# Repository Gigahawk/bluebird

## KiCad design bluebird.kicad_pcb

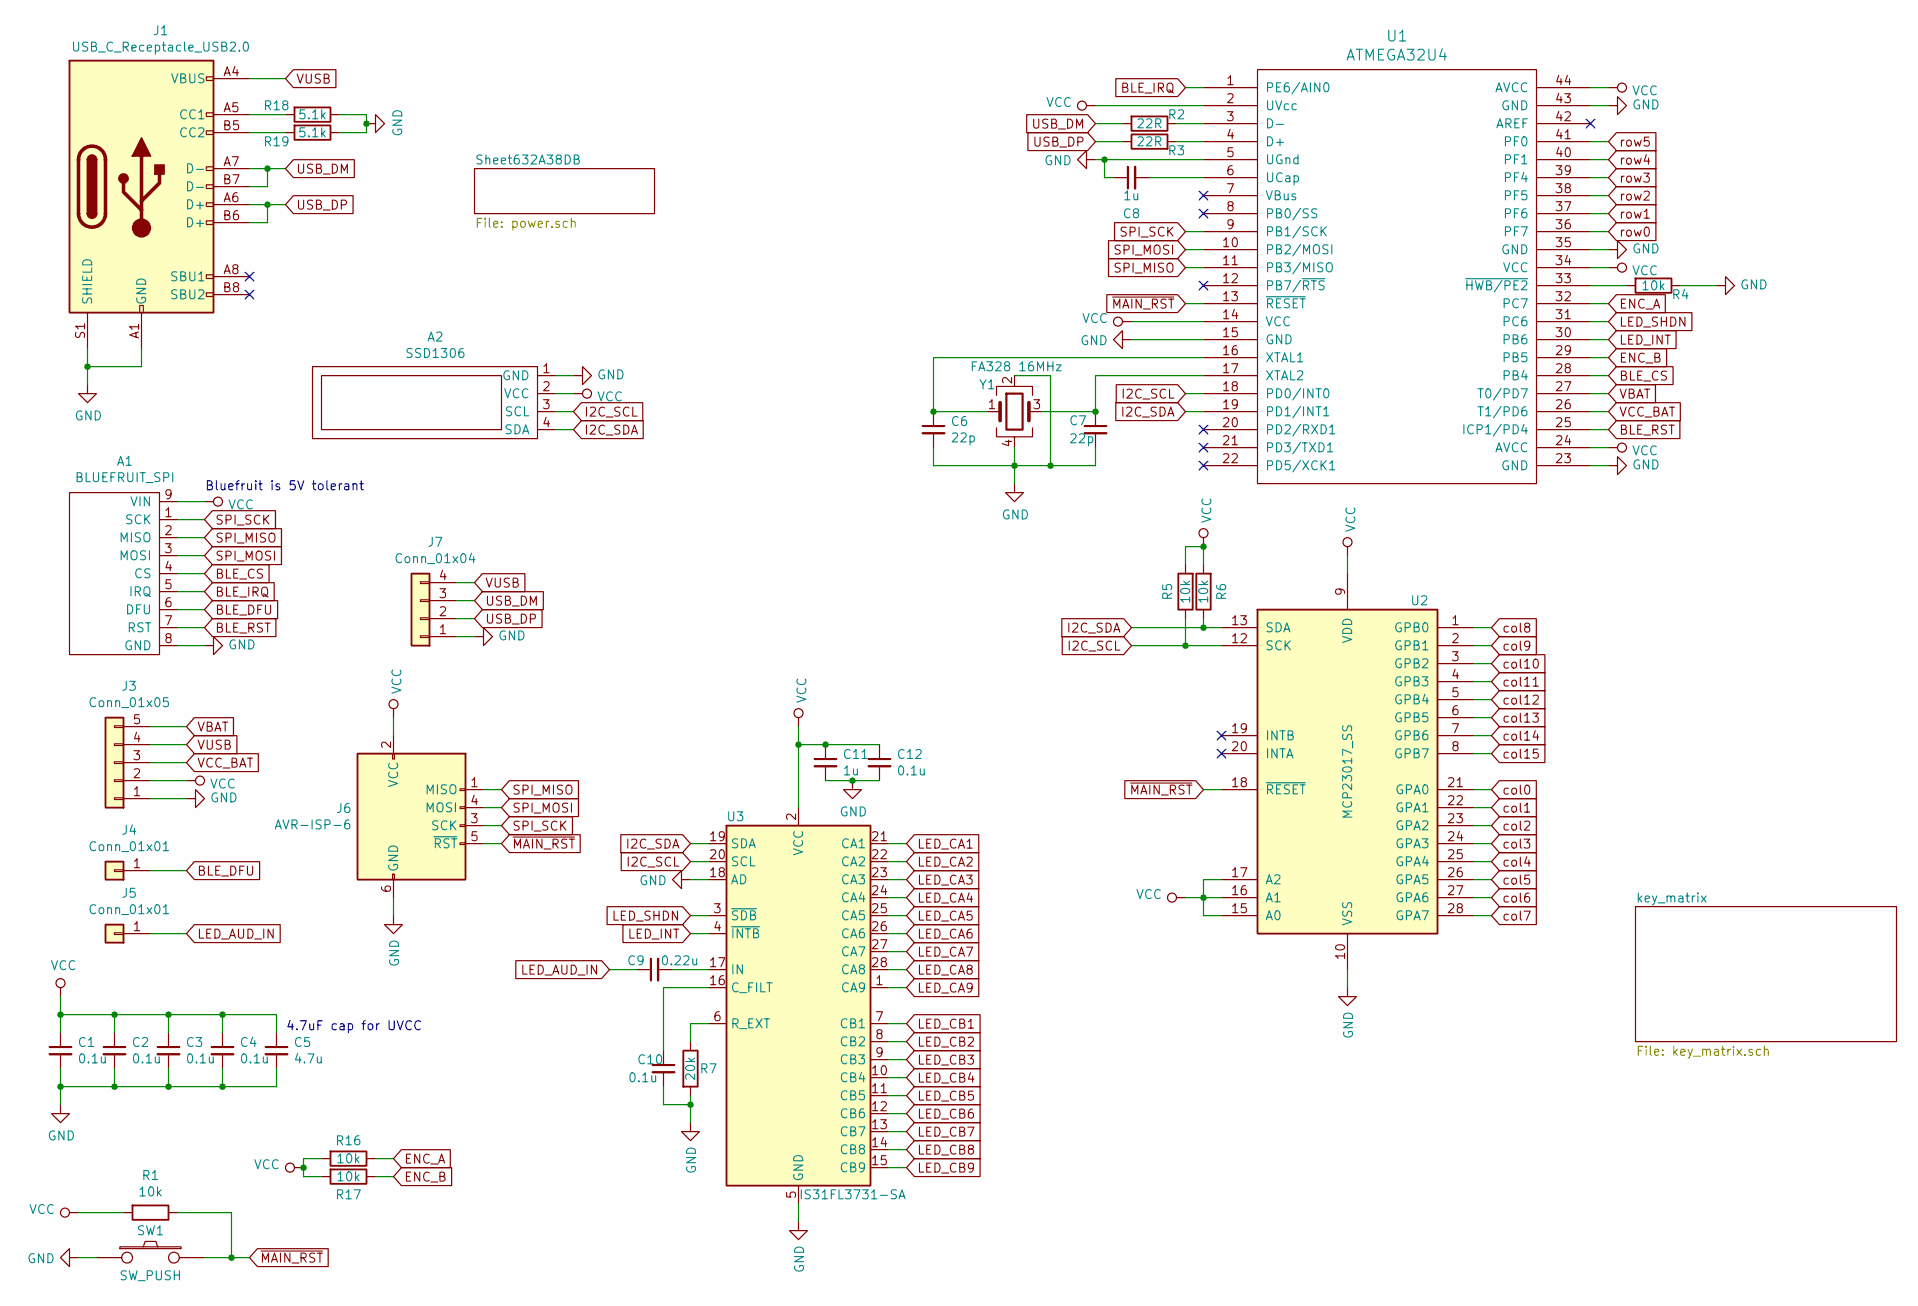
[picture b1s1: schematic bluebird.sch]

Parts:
A1: BLUEFRUIT_SPI; BLUEFRUIT_SPI_FRIEND
A2: SSD1306; SSD1306_128x32
C1, C2, C3, C4, C10, C12: 0.1u; C_0805_2012Metric_Pad1.15x1.40mm_HandSolder
C5: 4.7u; C_0805_2012Metric_Pad1.15x1.40mm_HandSolder
C6, C7: 22p; C_0805_2012Metric_Pad1.15x1.40mm_HandSolder
C8, C11: 1u; C_0805_2012Metric_Pad1.15x1.40mm_HandSolder
C9: 0.22u; C_0805_2012Metric_Pad1.15x1.40mm_HandSolder
J1: USB_C_Receptacle_USB2.0; USB_C_Receptacle_GCT_USB4085
J3: Conn_01x05; PinHeader_1x05_P2.54mm_Vertical
J4, J5: Conn_01x01; PinHeader_1x01_P2.54mm_Vertical
J6: AVR-ISP-6; AVR_ISP6
J7: Conn_01x04; PinHeader_1x04_P2.54mm_Vertical
R1, R4, R5, R6, R16, R17: 10k; R_0805_2012Metric_Pad1.15x1.40mm_HandSolder
R2, R3: 22R; R_0805_2012Metric_Pad1.15x1.40mm_HandSolder
R7: 20k; R_0805_2012Metric_Pad1.15x1.40mm_HandSolder
R18, R19: 5.1k; R_0805_2012Metric_Pad1.15x1.40mm_HandSolder
SW1: SW_PUSH; SW_SPST_TL3342
U1: ATMEGA32U4; TQFP-44_10x10mm_P0.8mm
U2: MCP23017_SS; SSOP-28_5.3x10.2mm_P0.65mm
U3: IS31FL3731-SA; SSOP-28_5.3x10.2mm_P0.65mm
Y1: FA328 16MHz; Crystal_SMD_SeikoEpson_FA238-4Pin_3.2x2.5mm_HandSoldering

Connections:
BLE_CS: A1.4 (CS), U1.28 (PB4)
BLE_DFU: A1.6 (DFU), J4.1
BLE_IRQ: A1.5 (IRQ), U1.1 (PE6/AIN0)
BLE_RST: A1.7 (RST), U1.25 (ICP1/PD4)
ENC_A: R16.1, U1.32 (PC7)
ENC_B: R17.1, U1.29 (PB5)
GND: A1.8 (GND), A2.1 (GND), C1.2, C2.2, C3.2, C4.2, C5.2, C6.2, C7.2, C8.1, C10.2, C11.2, C12.2, J1.A1 (GND), J1.A12 (GND), J1.B1 (GND), J1.B12 (GND), J1.S1 (SHIELD), J3.1, J6.6 (GND), J7.1, R4.1, R7.2, R18.1, R19.1, SW1.1, U1.5 (UGnd), U1.15 (GND), U1.23 (GND), U1.35 (GND), U1.43 (GND), U2.10 (VSS), U3.5 (GND), U3.18 (AD), Y1.2, Y1.4; also elsewhere on the board
I2C_SCL: A2.3 (SCL), R5.1, U1.18 (PD0/INT0), U2.12 (SCK), U3.20 (SCL)
I2C_SDA: A2.4 (SDA), R6.1, U1.19 (PD1/INT1), U2.13 (SDA), U3.19 (SDA)
LED_AUD_IN: C9.1, J5.1
LED_CA1: U3.21 (CA1); also elsewhere on the board
LED_CA2: U3.22 (CA2); also elsewhere on the board
LED_CA3: U3.23 (CA3); also elsewhere on the board
LED_CA4: U3.24 (CA4); also elsewhere on the board
LED_CA5: U3.25 (CA5); also elsewhere on the board
LED_CA6: U3.26 (CA6)
LED_CA7: U3.27 (CA7)
LED_CA8: U3.28 (CA8)
LED_CA9: U3.1 (CA9)
LED_CB1: U3.7 (CB1)
LED_CB2: U3.8 (CB2)
LED_CB3: U3.9 (CB3)
LED_CB4: U3.10 (CB4)
LED_CB5: U3.11 (CB5)
LED_CB6: U3.12 (CB6)
LED_CB7: U3.13 (CB7)
LED_CB8: U3.14 (CB8)
LED_CB9: U3.15 (CB9)
LED_INT: U1.30 (PB6), U3.4 (~INTB)
LED_SHDN: U1.31 (PC6), U3.3 (~SDB)
unnamed: C6.1, U1.16 (XTAL1), Y1.1
unnamed: C7.1, U1.17 (XTAL2), Y1.3
unnamed: C8.2, U1.6 (UCap)
unnamed: C9.2, U3.17 (IN)
unnamed: C10.1, U3.16 (C_FILT)
unnamed: J1.A5 (CC1), R18.2
unnamed: J1.B5 (CC2), R19.2
unnamed: R2.1, U1.3 (D-)
unnamed: R3.2, U1.4 (D+)
unnamed: R4.2, U1.33 (~HWB/PE2)
unnamed: R7.1, U3.6 (R_EXT)
SPI_MISO: A1.2 (MISO), J6.1 (MISO), U1.11 (PB3/MISO)
SPI_MOSI: A1.3 (MOSI), J6.4 (MOSI), U1.10 (PB2/MOSI)
SPI_SCK: A1.1 (SCK), J6.3 (SCK), U1.9 (PB1/SCK)
USB_DM: J1.A7 (D-), J1.B7 (D-), J7.3, R2.2
USB_DP: J1.A6 (D+), J1.B6 (D+), J7.2, R3.1
VBAT: J3.5, U1.27 (T0/PD7); also elsewhere on the board
VCC: A1.9 (VIN), A2.2 (VCC), C1.1, C2.1, C3.1, C4.1, C5.1, C11.1, C12.1, J3.2, J6.2 (VCC), R1.2, R5.2, R6.2, R16.2, R17.2, U1.2 (UVcc), U1.14 (VCC), U1.24 (AVCC), U1.34 (VCC), U1.44 (AVCC), U2.9 (VDD), U2.15 (A0), U2.16 (A1), U2.17 (A2), U3.2 (VCC); also elsewhere on the board
VCC_BAT: J3.3, U1.26 (T1/PD6); also elsewhere on the board
VUSB: J1.A4 (VBUS), J1.A9 (VBUS), J1.B4 (VBUS), J1.B9 (VBUS), J3.4, J7.4; also elsewhere on the board
col0: U2.21 (GPA0); also elsewhere on the board
col1: U2.22 (GPA1); also elsewhere on the board
col2: U2.23 (GPA2); also elsewhere on the board
col3: U2.24 (GPA3); also elsewhere on the board
col4: U2.25 (GPA4)
col5: U2.26 (GPA5)
col6: U2.27 (GPA6)
col7: U2.28 (GPA7)
col8: U2.1 (GPB0)
col9: U2.2 (GPB1)
col10: U2.3 (GPB2)
col11: U2.4 (GPB3)
col12: U2.5 (GPB4)
col13: U2.6 (GPB5)
col14: U2.7 (GPB6)
col15: U2.8 (GPB7)
row0: U1.36 (PF7); also elsewhere on the board
row1: U1.37 (PF6); also elsewhere on the board
row2: U1.38 (PF5); also elsewhere on the board
row3: U1.39 (PF4); also elsewhere on the board
row4: U1.40 (PF1); also elsewhere on the board
row5: U1.41 (PF0)
~MAIN_RST: J6.5 (~RST), R1.1, SW1.2, U1.13 (~RESET), U2.18 (~RESET~)

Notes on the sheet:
Bluefruit is 5V tolerant
4.7uF cap for UVCC

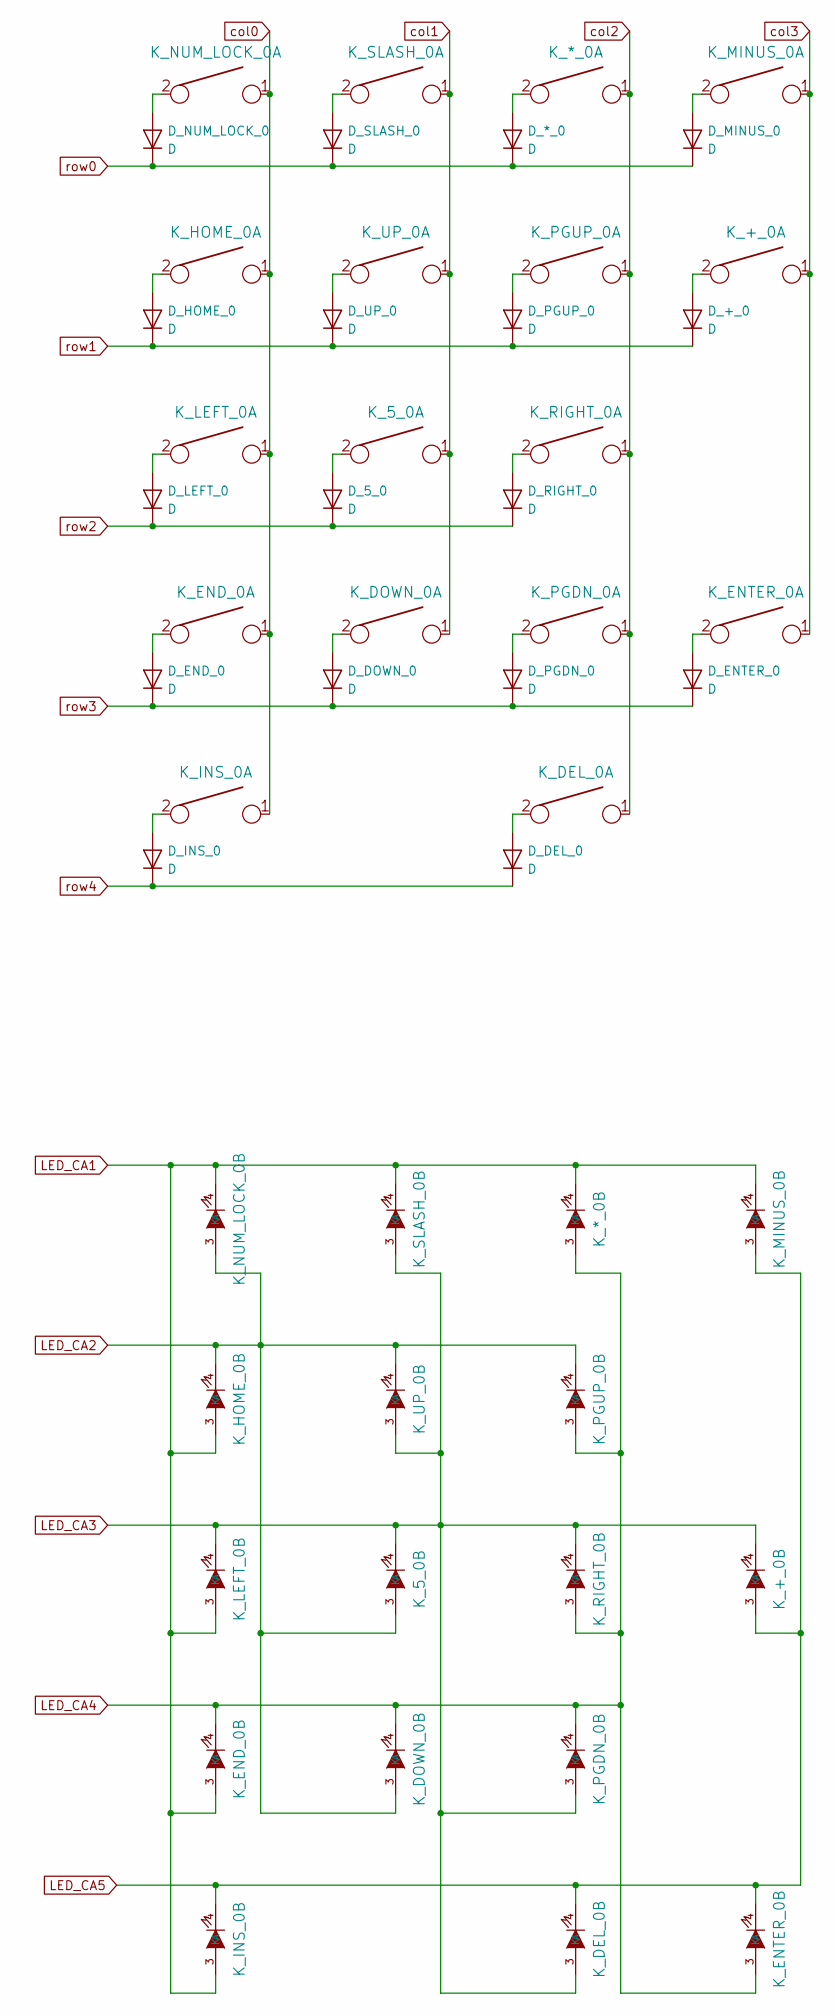
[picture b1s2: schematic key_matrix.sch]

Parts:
D_5_0: D; D_SOD123_axial
D_*_0: D; D_SOD123_axial
D_+_0: D; D_SOD123_axial
D_DEL_0: D; D_SOD123_axial
D_DOWN_0: D; D_SOD123_axial
D_END_0: D; D_SOD123_axial
D_ENTER_0: D; D_SOD123_axial
D_HOME_0: D; D_SOD123_axial
D_INS_0: D; D_SOD123_axial
D_LEFT_0: D; D_SOD123_axial
D_MINUS_0: D; D_SOD123_axial
D_NUM_LOCK_0: D; D_SOD123_axial
D_PGDN_0: D; D_SOD123_axial
D_PGUP_0: D; D_SOD123_axial
D_RIGHT_0: D; D_SOD123_axial
D_SLASH_0: D; D_SOD123_axial
D_UP_0: D; D_SOD123_axial
K_5_0: KEYSW; MX-1U
K_*_0: KEYSW; MX-1U
K_+_0: KEYSW; MX-2U
K_DEL_0: KEYSW; MX-1U
K_DOWN_0: KEYSW; MX-1U
K_END_0: KEYSW; MX-1U
K_ENTER_0: KEYSW; MX-2U
K_HOME_0: KEYSW; MX-1U
K_INS_0: KEYSW; MX-2U
K_LEFT_0: KEYSW; MX-1U
K_MINUS_0: KEYSW; MX-1U
K_NUM_LOCK_0: KEYSW; MX-1U
K_PGDN_0: KEYSW; MX-1U
K_PGUP_0: KEYSW; MX-1U
K_RIGHT_0: KEYSW; MX-1U
K_SLASH_0: KEYSW; MX-1U
K_UP_0: KEYSW; MX-1U

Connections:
LED_CA1: K_*_0.4 (K), K_END_0.3 (A), K_HOME_0.3 (A), K_INS_0.3 (A), K_LEFT_0.3 (A), K_MINUS_0.4 (K), K_NUM_LOCK_0.4 (K), K_SLASH_0.4 (K); also elsewhere on the board
LED_CA2: K_5_0.3 (A), K_DOWN_0.3 (A), K_HOME_0.4 (K), K_NUM_LOCK_0.3 (A), K_PGUP_0.4 (K), K_UP_0.4 (K); also elsewhere on the board
LED_CA3: K_5_0.4 (K), K_+_0.4 (K), K_DEL_0.3 (A), K_LEFT_0.4 (K), K_PGDN_0.3 (A), K_RIGHT_0.4 (K), K_SLASH_0.3 (A), K_UP_0.3 (A); also elsewhere on the board
LED_CA4: K_*_0.3 (A), K_DOWN_0.4 (K), K_END_0.4 (K), K_ENTER_0.3 (A), K_PGDN_0.4 (K), K_PGUP_0.3 (A), K_RIGHT_0.3 (A); also elsewhere on the board
LED_CA5: K_+_0.3 (A), K_DEL_0.4 (K), K_ENTER_0.4 (K), K_INS_0.4 (K), K_MINUS_0.3 (A); also elsewhere on the board
unnamed: D_5_0.2 (A), K_5_0.2
unnamed: D_*_0.2 (A), K_*_0.2
unnamed: D_+_0.2 (A), K_+_0.2
unnamed: D_DEL_0.2 (A), K_DEL_0.2
unnamed: D_DOWN_0.2 (A), K_DOWN_0.2
unnamed: D_END_0.2 (A), K_END_0.2
unnamed: D_ENTER_0.2 (A), K_ENTER_0.2
unnamed: D_HOME_0.2 (A), K_HOME_0.2
unnamed: D_INS_0.2 (A), K_INS_0.2
unnamed: D_LEFT_0.2 (A), K_LEFT_0.2
unnamed: D_MINUS_0.2 (A), K_MINUS_0.2
unnamed: D_NUM_LOCK_0.2 (A), K_NUM_LOCK_0.2
unnamed: D_PGDN_0.2 (A), K_PGDN_0.2
unnamed: D_PGUP_0.2 (A), K_PGUP_0.2
unnamed: D_RIGHT_0.2 (A), K_RIGHT_0.2
unnamed: D_SLASH_0.2 (A), K_SLASH_0.2
unnamed: D_UP_0.2 (A), K_UP_0.2
col0: K_END_0.1, K_HOME_0.1, K_INS_0.1, K_LEFT_0.1, K_NUM_LOCK_0.1; also elsewhere on the board
col1: K_5_0.1, K_DOWN_0.1, K_SLASH_0.1, K_UP_0.1; also elsewhere on the board
col2: K_*_0.1, K_DEL_0.1, K_PGDN_0.1, K_PGUP_0.1, K_RIGHT_0.1; also elsewhere on the board
col3: K_+_0.1, K_ENTER_0.1, K_MINUS_0.1; also elsewhere on the board
row0: D_*_0.1 (K), D_MINUS_0.1 (K), D_NUM_LOCK_0.1 (K), D_SLASH_0.1 (K); also elsewhere on the board
row1: D_+_0.1 (K), D_HOME_0.1 (K), D_PGUP_0.1 (K), D_UP_0.1 (K); also elsewhere on the board
row2: D_5_0.1 (K), D_LEFT_0.1 (K), D_RIGHT_0.1 (K); also elsewhere on the board
row3: D_DOWN_0.1 (K), D_END_0.1 (K), D_ENTER_0.1 (K), D_PGDN_0.1 (K); also elsewhere on the board
row4: D_DEL_0.1 (K), D_INS_0.1 (K); also elsewhere on the board

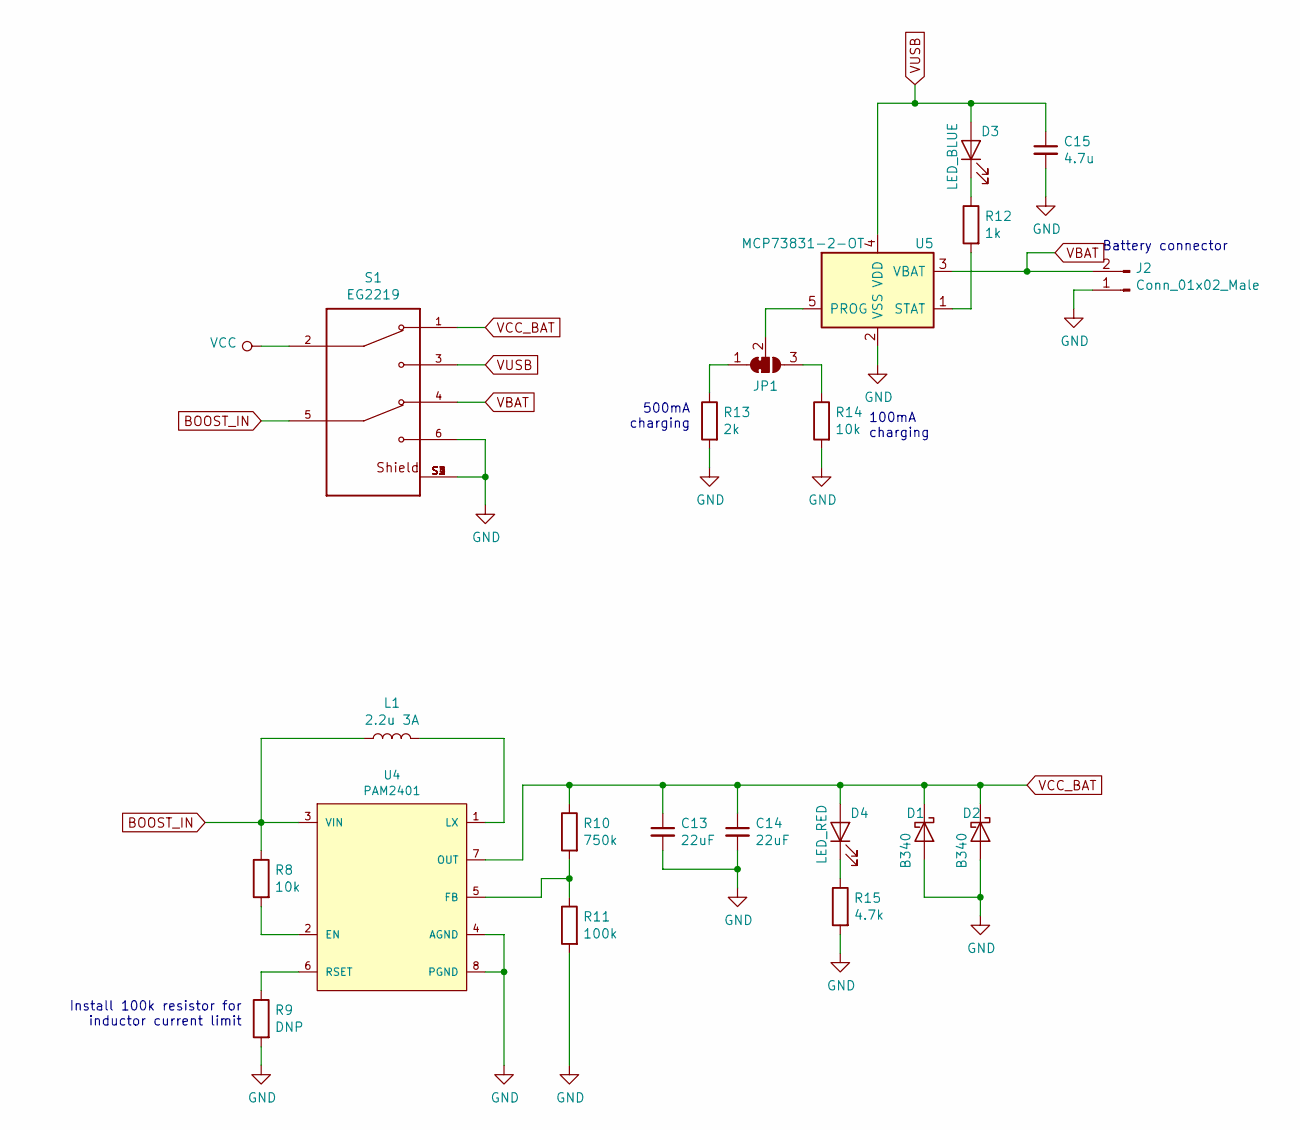
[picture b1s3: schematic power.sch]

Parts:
C13, C14: 22uF; C_0805_2012Metric_Pad1.15x1.40mm_HandSolder
C15: 4.7u; C_0805_2012Metric_Pad1.15x1.40mm_HandSolder
D1, D2: B340; D_SMC
D3: LED_BLUE; LED_0805_2012Metric
D4: LED_RED; LED_0805_2012Metric
J2: Conn_01x02_Male; JST_PH_S2B-PH-K_1x02_P2.00mm_Horizontal
JP1: SolderJumper_3_Bridged12; SolderJumper-3_P1.3mm_Bridged2Bar12_Pad1.0x1.5mm
L1: 2.2u 3A; L_Taiyo-Yuden_NR-50xx_HandSoldering
R8, R14: 10k; R_0805_2012Metric_Pad1.15x1.40mm_HandSolder
R9: DNP; R_0805_2012Metric_Pad1.15x1.40mm_HandSolder
R10: 750k; R_0805_2012Metric_Pad1.15x1.40mm_HandSolder
R11: 100k; R_0805_2012Metric_Pad1.15x1.40mm_HandSolder
R12: 1k; R_0805_2012Metric_Pad1.15x1.40mm_HandSolder
R13: 2k; R_0805_2012Metric_Pad1.15x1.40mm_HandSolder
R15: 4.7k; R_0805_2012Metric_Pad1.15x1.40mm_HandSolder
S1: EG2219; SW_EG2219
U4: PAM2401; MSOP8
U5: MCP73831-2-OT; SOT-23-5

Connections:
BOOST_IN: L1.1, R8.1, S1.5 (COM_5), U4.3 (VIN)
GND: C13.2, C14.2, C15.2, D1.2 (A), D2.2 (A), J2.1, R9.2, R11.2, R13.2, R14.2, R15.2, S1.6, S1.S1 (SHIELD), S1.S2 (SHIELD), S1.S3 (SHIELD), S1.S4 (SHIELD), U4.4 (AGND), U4.8 (PGND), U5.2 (VSS); also elsewhere on the board
unnamed: D3.1 (K), R12.1
unnamed: D4.1 (K), R15.1
unnamed: JP1.1 (A), R13.1
unnamed: JP1.2 (C), U5.5 (PROG)
unnamed: JP1.3 (B), R14.1
unnamed: L1.2, U4.1 (LX)
unnamed: R8.2, U4.2 (EN)
unnamed: R9.1, U4.6 (RSET)
unnamed: R10.2, R11.1, U4.5 (FB)
unnamed: R12.2, U5.1 (STAT)
VBAT: J2.2, S1.4, U5.3 (VBAT); also elsewhere on the board
VCC: S1.2 (COM_2); also elsewhere on the board
VCC_BAT: C13.1, C14.1, D1.1 (K), D2.1 (K), D4.2 (A), R10.1, S1.1, U4.7 (OUT); also elsewhere on the board
VUSB: C15.1, D3.2 (A), S1.3, U5.4 (VDD); also elsewhere on the board

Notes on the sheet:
Battery connector
Install 100k resistor for inductor current limit
500mA charging
100mA charging

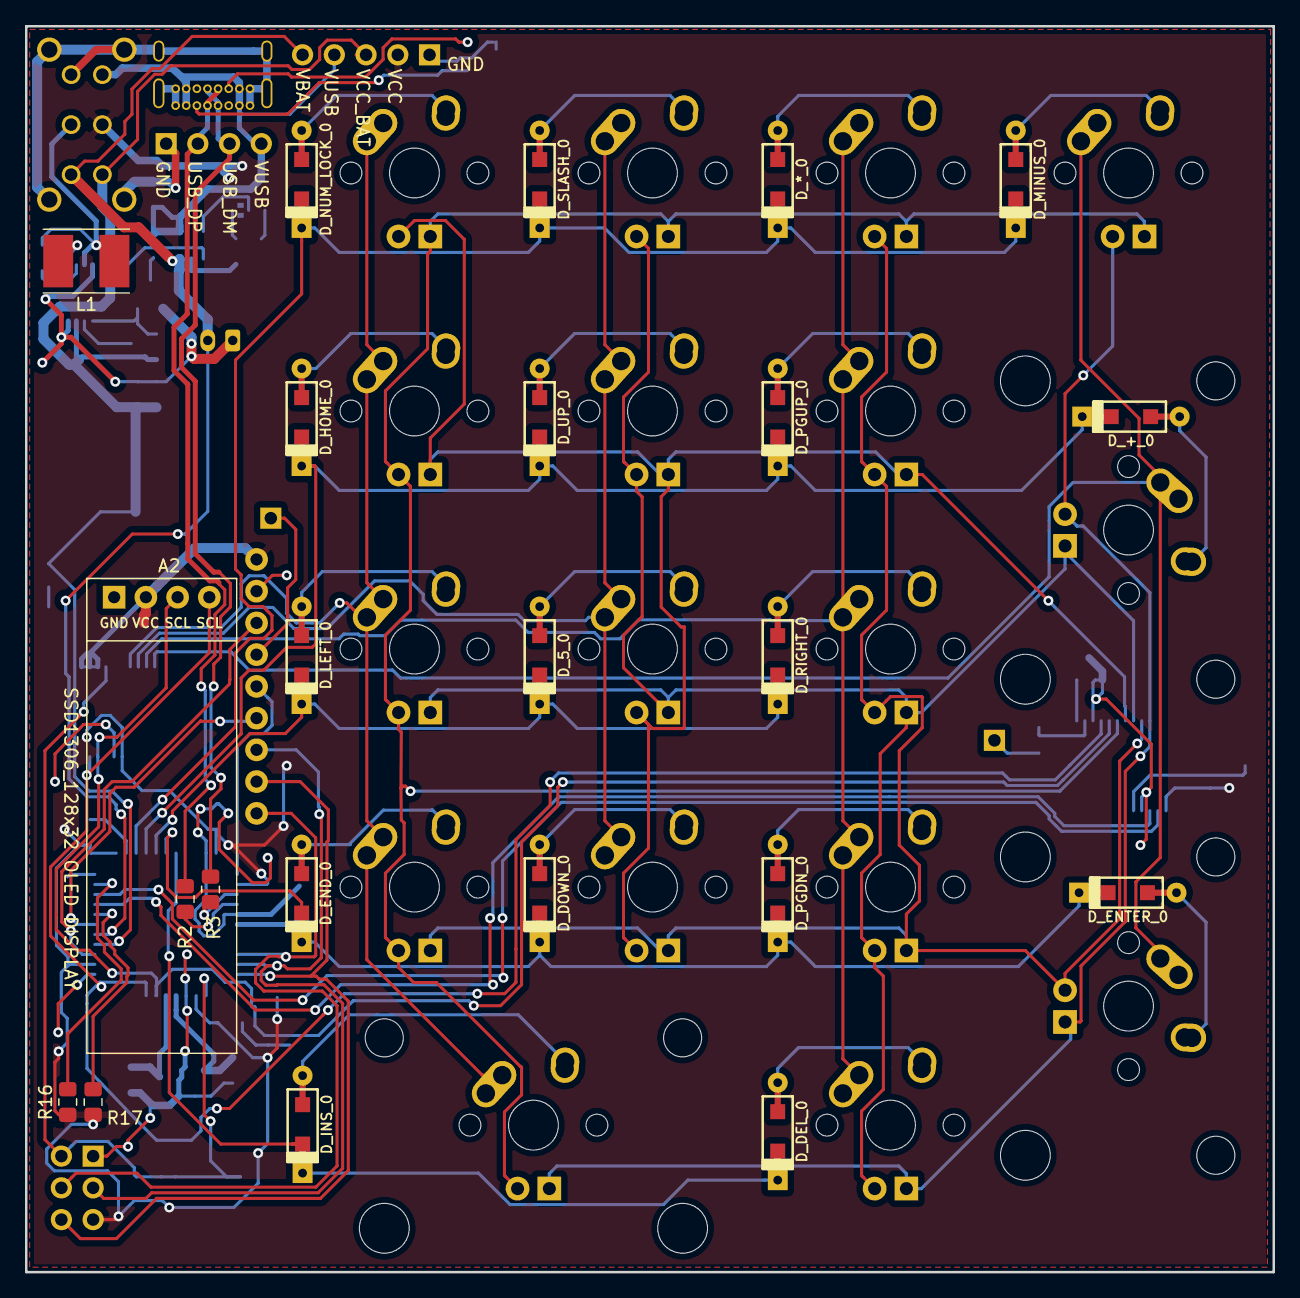
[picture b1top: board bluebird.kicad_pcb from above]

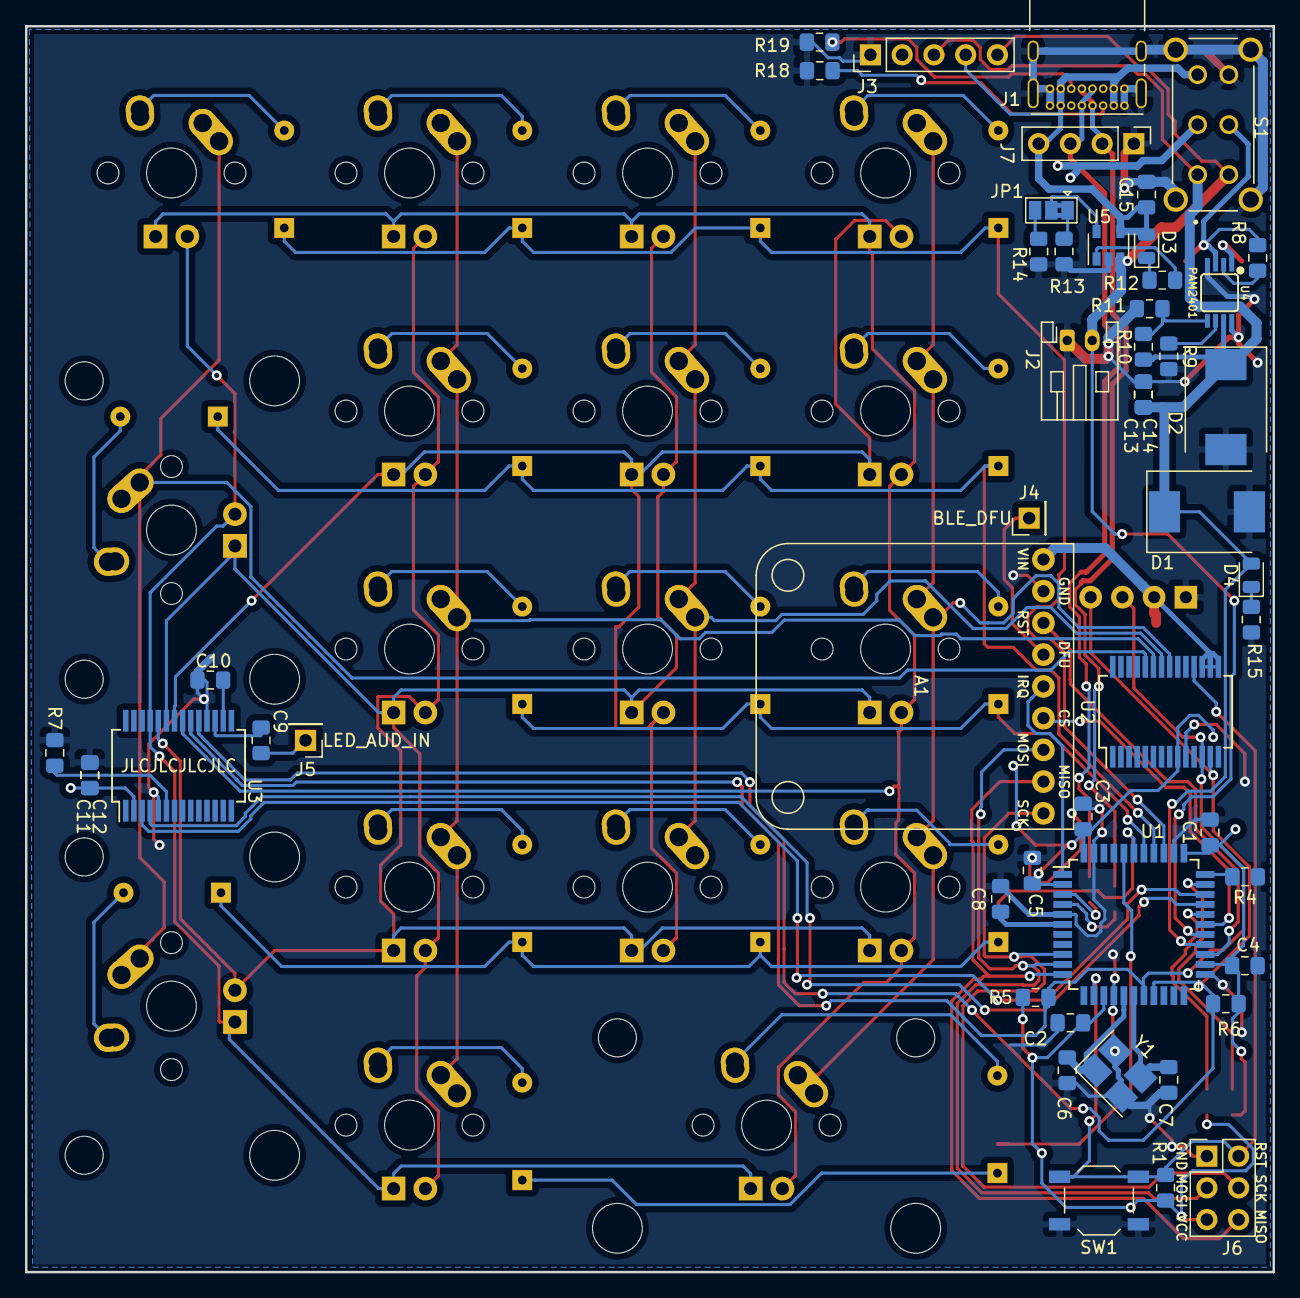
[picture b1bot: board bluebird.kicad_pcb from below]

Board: 2 copper layers, 99.8 x 99.7 mm, 91 parts (51 on the bottom side), 75 nets.

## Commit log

2020-03-17 Start schematic of core components
2020-03-18 Add and wire key matrix, IO expander
2020-03-19 Add LED controller + LEDS
2020-03-19 Wire LEDs into controller
2020-03-19 Finish charge controller, finish layout
2020-03-20 Route switches
2020-03-20 Attempt to wire LEDs
2020-03-20 Ripup all traces, rewire schematic matrix to better fit pcb layout
2020-03-20 Rewire as 4 layer board
2020-03-21 Add display and encoder
2020-03-21 Wire ISP/USB to debug headers
    Change L1 footprint
2020-03-22 Add wiring for battery indication
2020-03-23 Rewire as 2 layer numpad
2020-03-23 Add OSHW logo
2020-03-23 Unreverse diode labels
2020-06-12 Add USB C CC1/CC2 resistors, fix net overlaps.
    Add labels to testpoints.
